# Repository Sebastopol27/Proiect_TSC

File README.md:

## 1. Diagrama Bloc a Sistemului
Arhitectura hardware este centrata pe microcontrolerul nRF52840, gestionand distributia puterii, comunicatia cu senzorii si interfata vizuala.

      +----------+          +-----------+          +----------+
      |  USB 5V  | -------->|  BQ25180  | -------->|  RT6160  |
      +----------+          | (Charger) |          | (Reg)    |
                            +-----------+          +----------+
                                  ^                     |
                                  |                     | (3.3V Rail)
                                  v                     v
      +----------+          +-----------+          +----------+
      |   LiPo   | <------> |  BAT Node |          | nRF52840 |
      | Battery  |          +-----------+          |  (MCU)   |
      +----------+                |                +----------+
                                  v                     |
                            +-----------+               |
                            | MAX17048  | <-------------+ (I2C Bus)
                            | (Fuel G.) |               |
                            +-----------+               |
                                                        |
         +----------------------------------------------+
         |               |               |              |
         v (I2C)         v (I2C)         v (SPI)        v (GPIO)
   +-----------+   +-----------+   +-----------+   +------------+
   |  BMA421   |   | DRV2605L  |   |  E-Paper  |   | 3x Buttons |
   |  (Accel)  |   | (Haptic)  |   |  Display  |   +------------+
   +-----------+   +-----------+   +-----------+
                         |               ^
                         v               | (Power Gate)
                   +-----------+   +-----------+
                   |Vibe Motor |   | SI2301CDS |
                   +-----------+   |  (PFET)   |
                                   +-----------+

## 2. Bill of Materials (BOM)
Componentele sunt selectate pentru catalogul de asamblare JLCPCB.

| Functie      | Componenta     | Capsula    |
|--------------|----------------|------------|
| MCU          | nRF52840-QIAA  | aQFN73     | 
| Charger      | BQ25180YBGR    | DSBGA-8    |
| Regulator    | RT6160AWSC     | WLCSP-15   |
| Fuel Gauge   | MAX17048G+T10  | DFN-8      |
| Accel        | BMA421         | LGA-12     |
| Haptic Drv   | DRV2605LDGSR   | VSSOP-10   |
| Vibe Motor   | LCM1027B3605F  | Wire       |
| EPD PFET     | SI2301CDS      | SOT-23     |

## 3. Functionalitate Hardware in Detaliu

### Managementul Puterii (Power Tree)
[cite_start]Sistemul utilizeaza o arhitectura tip "power-path":
* **BQ25180**: Gestioneaza incarcarea bateriei LiPo de 250 mAh si asigura tranzitia automata intre alimentarea USB si baterie.
* **RT6160**: Regulator buck-boost setat pentru o iesire de 3.3V (VSEL low), asigurand stabilitatea MCU-ului pe toata durata de descarcare a bateriei.
* **MAX17048**: Monitorizeaza precis tensiunea bateriei si starea de incarcare (SOC) prin masurare directa pe VBAT.

### Senzori si Interfete
* **Magistrala I2C**: Partajata intre accelerometru, fuel gauge, charger, regulator si driverul haptic.
* **Interfata SPI**: Utilizata exclusiv pentru controller-ul ecranului e-paper.
* **BMA421**: Detecteaza pașii mereu activ si trimite intreruperi hardware (INT1) catre MCU pentru wake-up.
* **Haptics**: Driverul DRV2605L controleaza motorul ERM pentru alerte tactile, fiind activat (EN) doar in timpul utilizarii pentru a economisi energie.

### Calcule si Eficienta Consumului
* **Power Gating**: Un PFET (SI2301) controlat de MCU (P1.01) intrerupe alimentarea ecranului e-paper (VEPD) cand acesta nu se afla intr-un ciclu de refresh.
* **Tinta Autonomie**: >= 30 de zile cu refresh de ecran o data pe minut si maxim 50 de notificari zilnice.

## 4. Alocarea Pinilor nRF52840

Pinii au fost selectati pentru a optimiza rutarea pe un PCB cu 4 straturi.

| Componenta      | Pin MCU       | Justificare / Functie |
|-----------------|---------------|-----------------------|
| **I2C SDA** | P0.06  | Comunicatie date senzori si IC-uri power. |
| **I2C SCL** | P0.07 | Ceas magistrala I2C (10k pull-up extern). |
| **SPI SCK** | P0.02 | Ceas SPI pentru transfer rapid display. |
| **SPI MOSI** | P0.03 | Date seriale catre ecran e-paper. |
| **SPI CS** | P0.05 | Selectie chip afisaj (Chip Select). |
| **EPD DC** | P0.15 | Selectie Data/Command pentru display. |
| **EPD RST** | P0.16 | Reset hardware display. |
| **EPD Busy** | P0.17 | Monitorizare stare procesare refresh ecran. |
| **EPD Power** | P1.01 | Poarta PFET pentru management alimentare VEPD. |
| **Accel INT** | P0.08 | INT1 (wake primar pentru pedometru). |
| **Accel INT2** | P1.08 | INT2 pentru evenimente secundare. |
| **Fuel Gauge** | P0.10 | ALRT pentru prag baterie descarcata. |
| **Charger INT** | P0.11 | Intrerupere pentru evenimente de incarcare. |
| **Haptic EN** | P0.12 | Enable pentru oprirea driverului haptic. |
| **Buttons** | P0.13, P0.14 | Up si Down (active low, wake source). |
| **Button Ent** | P1.00 | Enter / Esc (active low). |

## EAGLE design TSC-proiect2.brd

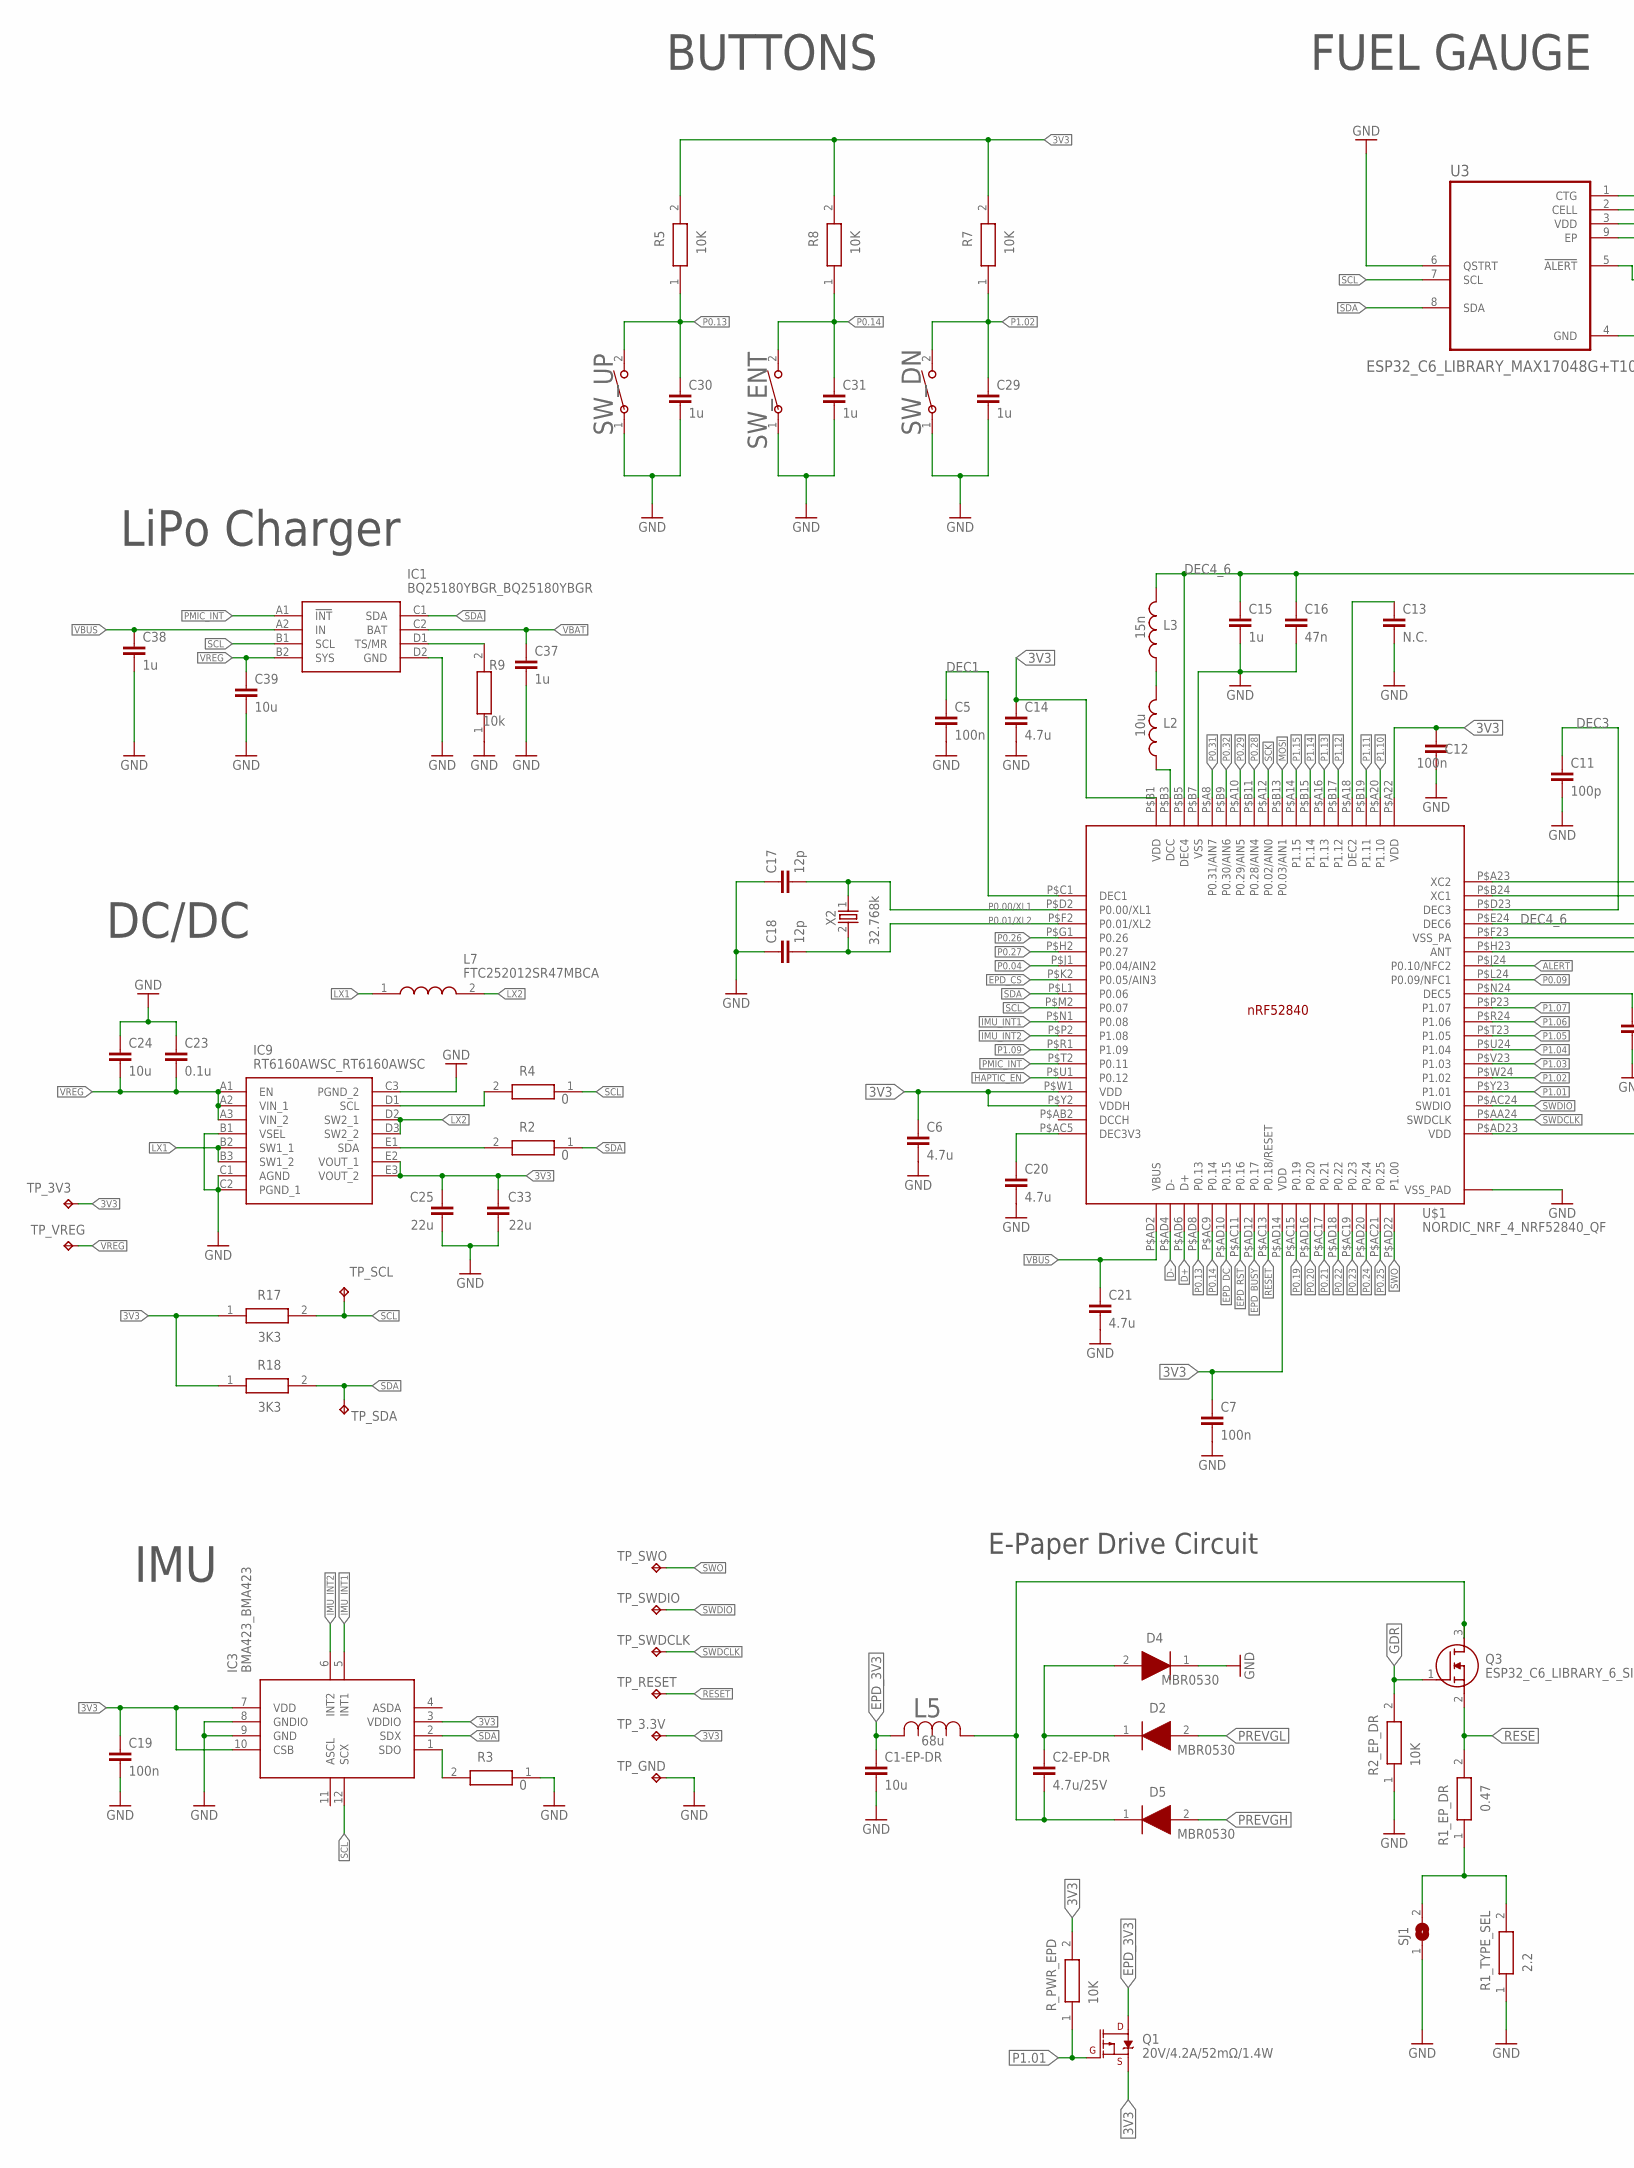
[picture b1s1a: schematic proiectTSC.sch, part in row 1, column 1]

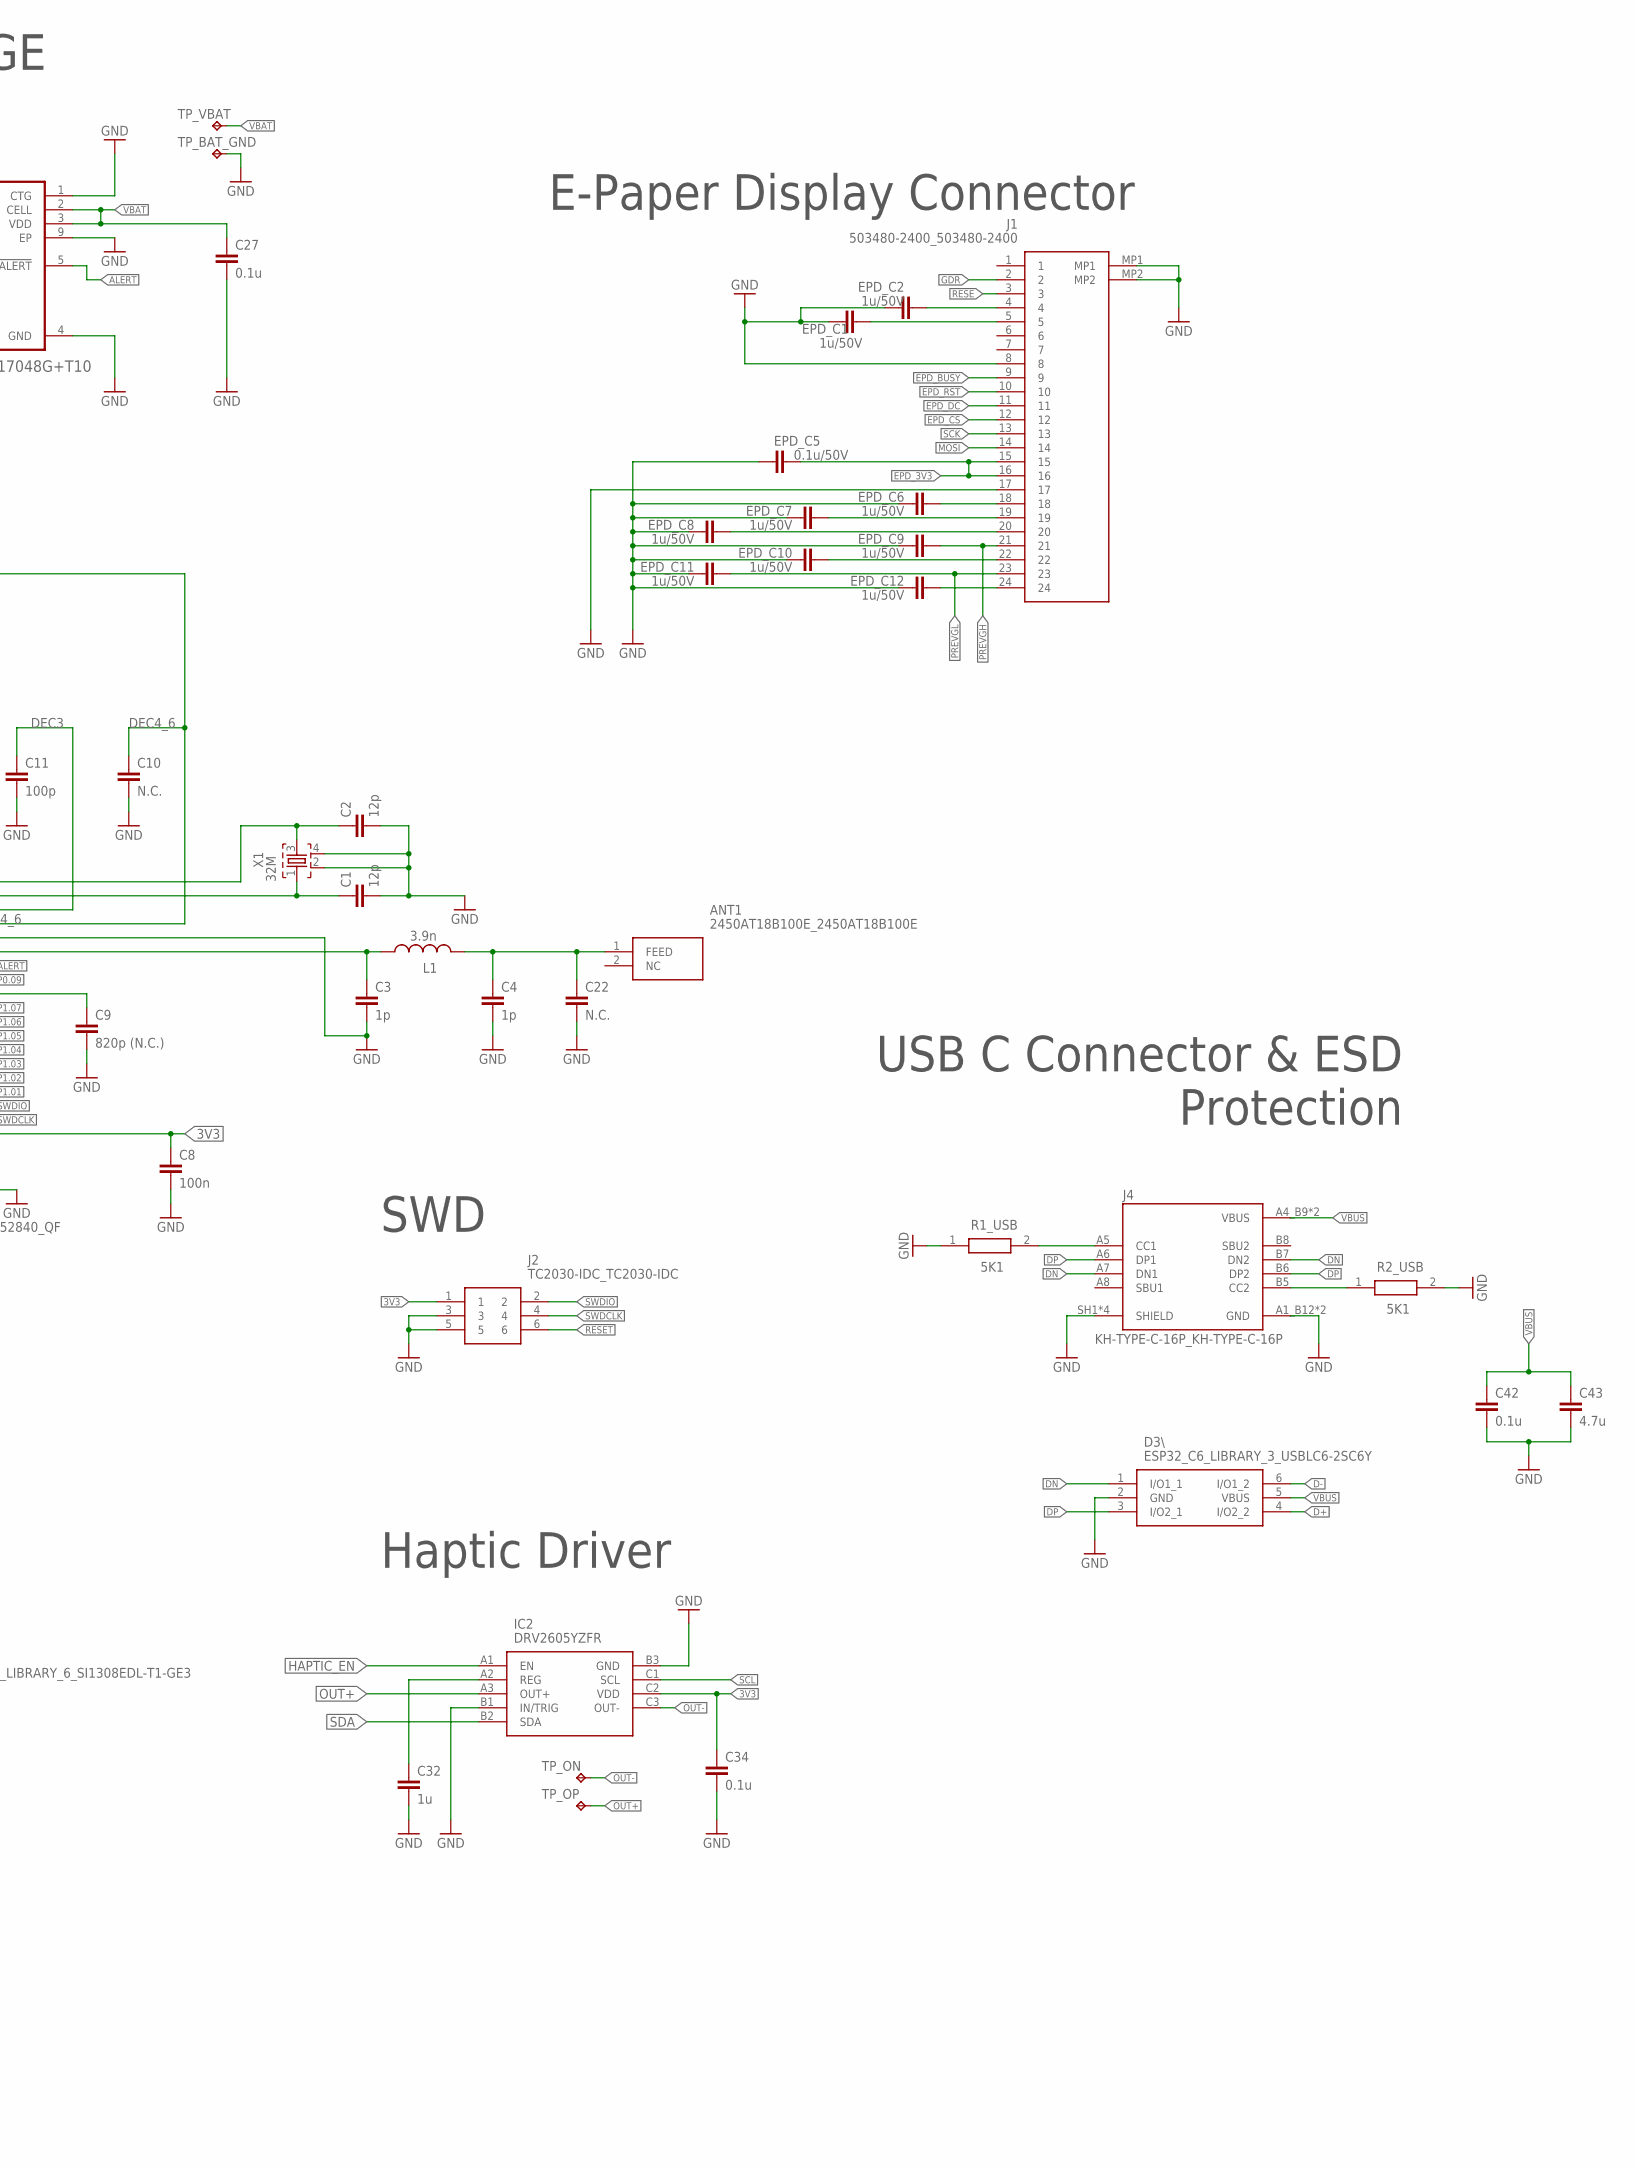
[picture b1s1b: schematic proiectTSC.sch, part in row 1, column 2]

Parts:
ANT1: 2450AT18B100E_2450AT18B100E; 2450AT18B100E_ANTC3216X140N
C1, C2, C17, C18: 12p; NORDIC_NRF_3_RESC0201_L
C1-EP-DR, C24, C39: 10u; PERFECT_0402_0402
C2-EP-DR: 4.7u/25V; NORDIC_NRF_3_RESC0603_L
C3, C4: 1p; NORDIC_NRF_3_RESC0201_L
C5, C7, C8, C12, C19: 100n; NORDIC_NRF_3_RESC0201_L
C6, C14, C20, C21, C43: 4.7u; PERFECT_0402_0402
C9: 820p (N.C.); NORDIC_NRF_3_RESC0201_L
C10, C22: N.C.; NORDIC_NRF_3_RESC0201_L
C11: 100p; NORDIC_NRF_3_RESC0201_L
C13: N.C.; PERFECT_0402_0402
C15, C29, C30, C31, C32, C37, C38: 1u; PERFECT_0402_0402
C16: 47n; NORDIC_NRF_3_RESC0201_L
C23, C27, C34, C42: 0.1u; NORDIC_NRF_3_RESC0201_L
C25: 22u; NORDIC_NRF_3_RESC0201_L
C33: 22u; PERFECT_0402_0402
D2, D4, D5: MBR0530; ESP32_C6_LIBRARY_5_SOD3716X135N
D3\: ESP32_C6_LIBRARY_3_USBLC6-2SC6Y; ESP32_C6_LIBRARY_3_SOT95P280X145-6N
EPD_C1, EPD_C2, EPD_C6, EPD_C7, EPD_C8, EPD_C9, EPD_C10, EPD_C11, EPD_C12: 1u/50V; NORDIC_NRF_3_RESC0603_L
EPD_C5: 0.1u/50V; NORDIC_NRF_3_RESC0603_L
IC1: BQ25180YBGR_BQ25180YBGR; BQ25180YBGR_BGA8C40P2X4_100X155X50
IC2: DRV2605YZFR; DRV2605YZFR_BGA9C50P3X3_144X144X62
IC3: BMA423_BMA423
IC9: RT6160AWSC_RT6160AWSC; RT6160AWSC_BGA15C40P3X5_140X230X60
J1: 503480-2400_503480-2400; 503480-2400_5034802400
J2: TC2030-IDC_TC2030-IDC; TC2030-IDC_TC2030IDC
J4: KH-TYPE-C-16P_KH-TYPE-C-16P; KH-TYPE-C-16P_KINGHELM_KH-TYPE-C-16P
L1: 3.9n; NORDIC_NRF_2_RESC0201_L
L2: 10u; NORDIC_NRF_2_RESC0402_L
L3: 15n; NORDIC_NRF_2_RESC0201_L
L5: 68u; ESP32_C6_LIBRARY_2_IND_4828-WE-TPC_WRE
L7: FTC252012SR47MBCA; MLP2016SR47MT0S1_INDC2016X100N
Q1: 20V/4.2A/52mΩ/1.4W; ESP32_C6_LIBRARY_4_ESP32_C6_LIBRARY_4_ESP32_C6_LIBRARY_4_ES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
Q3: ESP32_C6_LIBRARY_6_SI1308EDL-T1-GE3; ESP32_C6_LIBRARY_6_SOT65P210X110-3N
R1_EP_DR: 0.47; CPF0201D7K68C1_0201
R1_TYPE_SEL: 2.2; CPF0201D7K68C1_0201
R1_USB, R2_USB: 5K1; CPF0201D7K68C1_0201
R2, R3, R4: 0; CPF0201D7K68C1_0201
R2_EP_DR, R5, R7, R8: 10K; CPF0201D7K68C1_0201
R9: 10k; CPF0201D7K68C1_0201
R17, R18: 3K3; CPF0201D7K68C1_0201
R_PWR_EPD: 10K; CPF0201D7K68C1_0201
SJ1: ESP32_C6_LIBRARY_7_JUMPER_SJ
SW_DN: 2025-10-22_07-23-44_LIBRARY_EVP-AKE31ASW_EVP-AKE3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; 2025-10-22_07-23-44_LIBRARY_SW_EVP-AKE31A_PAN
SW_ENT: 2025-10-22_07-23-44_LIBRARY_EVP-AKE31ASW_EVP-AKE3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; 2025-10-22_07-23-44_LIBRARY_SW_EVP-AKE31A_PAN
SW_UP: 2025-10-22_07-23-44_LIBRARY_EVP-AKE31ASW_EVP-AKE3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; 2025-10-22_07-23-44_LIBRARY_SW_EVP-AKE31A_PAN
TP_3.3V, TP_3V3: HECTOR_WATCH_1_TPTP20R; HECTOR_WATCH_1_TP20R
TP_BAT_GND: HECTOR_WATCH_1_TPTP20R; HECTOR_WATCH_1_TP20R
TP_GND: HECTOR_WATCH_1_TPTP20R; HECTOR_WATCH_1_TP20R
TP_ON: HECTOR_WATCH_1_TPTP20R; HECTOR_WATCH_1_TP20R
TP_OP: HECTOR_WATCH_1_TPTP20R; HECTOR_WATCH_1_TP20R
TP_RESET: HECTOR_WATCH_1_TPTP20R; HECTOR_WATCH_1_TP20R
TP_SCL: HECTOR_WATCH_1_TPTP20R; HECTOR_WATCH_1_TP20R
TP_SDA: HECTOR_WATCH_1_TPTP20R; HECTOR_WATCH_1_TP20R
TP_SWDCLK: HECTOR_WATCH_1_TPTP20R; HECTOR_WATCH_1_TP20R
TP_SWDIO: HECTOR_WATCH_1_TPTP20R; HECTOR_WATCH_1_TP20R
TP_SWO: HECTOR_WATCH_1_TPTP20R; HECTOR_WATCH_1_TP20R
TP_VBAT: HECTOR_WATCH_1_TPTP20R; HECTOR_WATCH_1_TP20R
TP_VREG: HECTOR_WATCH_1_TPTP20R; HECTOR_WATCH_1_TP20R
U3: ESP32_C6_LIBRARY_MAX17048G+T10; ESP32_C6_LIBRARY_SON50P200X200X80-9N
U$1: NORDIC_NRF_4_NRF52840_QF; NORDIC_NRF_4_AQFN50P700X700X85_HS-74N
X1: 32M; NORDIC_NRF_BT-XTAL_2016_N
X2: 32.768k; NORDIC_NRF_1_XTAL_3215_N

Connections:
ALERT: U3.5 (!ALERT), U$1.P$J24 (P0.10/NFC2)
D+: D3\.4 (I/O2_2), U$1.P$AD6 (D+)
D-: D3\.6 (I/O1_2), U$1.P$AD4 (D-)
DEC1: C5.1, U$1.P$C1 (DEC1)
DEC3: C11.1, U$1.P$D23 (DEC3)
DEC4_6: C10.1, C15.1, C16.1, L3.2, U$1.P$B5 (DEC4), U$1.P$E24 (DEC6)
DN: D3\.1 (I/O1_1), J4.A7 (DN1), J4.B7 (DN2)
DP: D3\.3 (I/O2_1), J4.A6 (DP1), J4.B6 (DP2)
EPD_3V3: C1-EP-DR.1, EPD_C5.2, J1.15, J1.16, L5.2, Q1.3 (D)
EPD_BUSY: J1.9, U$1.P$AD12 (P0.17)
EPD_CS: J1.12, U$1.P$K2 (P0.05/AIN3)
EPD_DC: J1.11, U$1.P$AD10 (P0.15)
EPD_RST: J1.10, U$1.P$AC11 (P0.16)
GDR: J1.2, Q3.1 (G), R2_EP_DR.2
GND: C1.2, C1-EP-DR.2, C2.2, C3.2, C4.2, C5.2, C6.2, C7.2, C8.2, C9.2, C10.2, C11.2, C12.2, C13.2, C14.2, C15.2, C16.2, C17.1, C18.1, C19.2, C20.2, C21.2, C22.2, C23.1, C24.1, C25.1, C27.2, C29.2, C30.2, C31.2, C32.2, C33.1, C34.2, C37.2, C38.2, C39.2, C42.2, C43.2, D3\.2 (GND), D4.1 (K), EPD_C1.1, EPD_C2.1, EPD_C5.1, EPD_C6.1, EPD_C7.1, EPD_C8.1, EPD_C9.1, EPD_C10.1, EPD_C11.1, EPD_C12.1, IC1.D2 (GND), IC2.B1 (IN/TRIG), IC2.B3 (GND), IC3.8 (GNDIO), IC3.9 (GND), IC9.B1 (VSEL), IC9.C1 (AGND), IC9.C2 (PGND_1), IC9.C3 (PGND_2), J1.8, J1.17, J1.MP1, J1.MP2, J2.3, J2.5, J4.A1_B12 (GND), J4.A12_B1 (GND), J4.SH1 (SHIELD), J4.SH2 (SHIELD), J4.SH3 (SHIELD), J4.SH4 (SHIELD), R1_TYPE_SEL.1, R1_USB.1, R2_EP_DR.1, R2_USB.2, R3.1, R9.1, SJ1.1, SW_DN.1, SW_ENT.1, SW_UP.1, TP_BAT_GND.TP, TP_GND.TP, U3.1 (CTG), U3.4 (GND), U3.6 (QSTRT), U3.9 (EP), U$1.P$74 (VSS_PAD), U$1.P$75 (VSS_PAD), U$1.P$76 (VSS_PAD), U$1.P$77 (VSS_PAD), U$1.P$78 (VSS_PAD), U$1.P$79 (VSS_PAD), U$1.P$80 (VSS_PAD), U$1.P$81 (VSS_PAD), U$1.P$82 (VSS_PAD), U$1.P$83 (VSS_PAD), U$1.P$84 (VSS_PAD), U$1.P$85 (VSS_PAD), U$1.P$86 (VSS_PAD), U$1.P$87 (VSS_PAD), U$1.P$88 (VSS_PAD), U$1.P$89 (VSS_PAD), U$1.P$90 (VSS_PAD), U$1.P$B7 (VSS), U$1.P$F23 (VSS_PA), X1.2, X1.4
HAPTIC_EN: IC2.A1 (EN), U$1.P$U1 (P0.12)
IMU_INT1: IC3.5 (INT1), U$1.P$N1 (P0.08)
IMU_INT2: IC3.6 (INT2), U$1.P$P2 (P1.08)
LX1: IC9.B2 (SW1_1), IC9.B3 (SW1_2), L7.1
LX2: IC9.D2 (SW2_1), IC9.D3 (SW2_2), L7.2
MOSI: J1.14, U$1.P$B13 (P0.03/AIN1)
unnamed: L2.1, U$1.P$B3 (DCC)
unnamed: L2.2, L3.1
unnamed: C13.1, U$1.P$A18 (DEC2)
unnamed: C20.1, U$1.P$AC5 (DEC3V3)
unnamed: C9.1, U$1.P$N24 (DEC5)
unnamed: C3.1, L1.1, U$1.P$H23 (ANT)
unnamed: ANT1.1 (FEED), C4.1, C22.1, L1.2
unnamed: C1.1, U$1.P$B24 (XC1), X1.1
unnamed: C2.1, U$1.P$A23 (XC2), X1.3
unnamed: IC1.D1 (TS/MR), R9.2
unnamed: IC9.D1 (SCL), R4.2
unnamed: IC9.E1 (SDA), R2.2
unnamed: R17.1, R18.1
unnamed: R1_EP_DR.1, R1_TYPE_SEL.2, SJ1.2
unnamed: C32.1, IC2.A2 (REG)
unnamed: C2-EP-DR.1, D2.1 (K), D4.2 (A)
unnamed: C2-EP-DR.2, D5.1 (K), L5.1, Q3.3 (D)
unnamed: IC3.1 (SDO), R3.2
unnamed: EPD_C6.2, J1.18
unnamed: EPD_C7.2, J1.19
unnamed: EPD_C2.2, J1.4
unnamed: EPD_C1.2, J1.5
unnamed: EPD_C8.2, J1.20
unnamed: EPD_C10.2, J1.22
unnamed: EPD_C12.2, J1.24
unnamed: J4.B5 (CC2), R2_USB.1
unnamed: J4.A5 (CC1), R1_USB.2
OUT+: IC2.A3 (OUT+), TP_OP.TP
OUT-: IC2.C3 (OUT-), TP_ON.TP
P0.00/XL1: C17.2, U$1.P$D2 (P0.00/XL1), X2.1
P0.01/XL2: C18.2, U$1.P$F2 (P0.01/XL2), X2.2
P0.04: U$1.P$J1 (P0.04/AIN2)
P0.09: U$1.P$L24 (P0.09/NFC1)
P0.13: C30.1, R5.1, SW_UP.2, U$1.P$AD8 (P0.13)
P0.14: C31.1, R8.1, SW_ENT.2, U$1.P$AC9 (P0.14)
P0.19: U$1.P$AC15 (P0.19)
P0.20: U$1.P$AD16 (P0.20)
P0.21: U$1.P$AC17 (P0.21)
P0.22: U$1.P$AD18 (P0.22)
P0.23: U$1.P$AC19 (P0.23)
P0.24: U$1.P$AD20 (P0.24)
P0.25: U$1.P$AC21 (P0.25)
P0.26: U$1.P$G1 (P0.26)
P0.27: U$1.P$H2 (P0.27)
P0.28: U$1.P$B11 (P0.28/AIN4)
P0.29: U$1.P$A10 (P0.29/AIN5)
P0.31: U$1.P$A8 (P0.31/AIN7)
P0.32: U$1.P$B9 (P0.30/AIN6)
P1.01: Q1.1 (G), R_PWR_EPD.1, U$1.P$Y23 (P1.01)
P1.02: C29.1, R7.1, SW_DN.2, U$1.P$W24 (P1.02)
P1.03: U$1.P$V23 (P1.03)
P1.04: U$1.P$U24 (P1.04)
P1.05: U$1.P$T23 (P1.05)
P1.06: U$1.P$R24 (P1.06)
P1.07: U$1.P$P23 (P1.07)
P1.09: U$1.P$R1 (P1.09)
P1.10: U$1.P$A20 (P1.10)
P1.11: U$1.P$B19 (P1.11)
P1.12: U$1.P$B17 (P1.12)
P1.13: U$1.P$A16 (P1.13)
P1.14: U$1.P$B15 (P1.14)
P1.15: U$1.P$A14 (P1.15)
PMIC_INT: IC1.A1 (!INT), U$1.P$T2 (P0.11)
PREVGH: D5.2 (A), EPD_C9.2, J1.21
PREVGL: D2.2 (A), EPD_C11.2, J1.23
RESE: J1.3, Q3.2 (S), R1_EP_DR.2
RESET: J2.6, TP_RESET.TP, U$1.P$AC13 (P0.18/RESET)
SCK: J1.13, U$1.P$A12 (P0.02/AIN0)
SWDCLK: J2.4, TP_SWDCLK.TP, U$1.P$AA24 (SWDCLK)
SWDIO: J2.2, TP_SWDIO.TP, U$1.P$AC24 (SWDIO)
SWO: TP_SWO.TP, U$1.P$AD22 (P1.00)
VBAT: C27.1, C37.1, IC1.C2 (BAT), TP_VBAT.TP, U3.2 (CELL), U3.3 (VDD)
VBUS: C21.1, C38.1, C42.1, C43.1, D3\.5 (VBUS), IC1.A2 (IN), J4.A4_B9 (VBUS), J4.A9_B4 (VBUS), U$1.P$AD2 (VBUS)
VREG: C23.2, C24.2, C39.1, IC1.B2 (SYS), IC9.A1 (EN), IC9.A2 (VIN_1), IC9.A3 (VIN_2), TP_VREG.TP

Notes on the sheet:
LiPo Charger
DC/DC
IMU
SWD
E-Paper Drive Circuit
Haptic Driver
BUTTONS
FUEL GAUGE
E-Paper Display Connector
USB C Connector & ESD Protection

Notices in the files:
parts and their libraries:
InkTime_v5: COPYRIGHT: Copyright (C) 2024 Ultra Librarian. All rights reserved.
InkTime_v5: COPYRIGHT: Copyright (C) 2025 Ultra Librarian. All rights reserved.
